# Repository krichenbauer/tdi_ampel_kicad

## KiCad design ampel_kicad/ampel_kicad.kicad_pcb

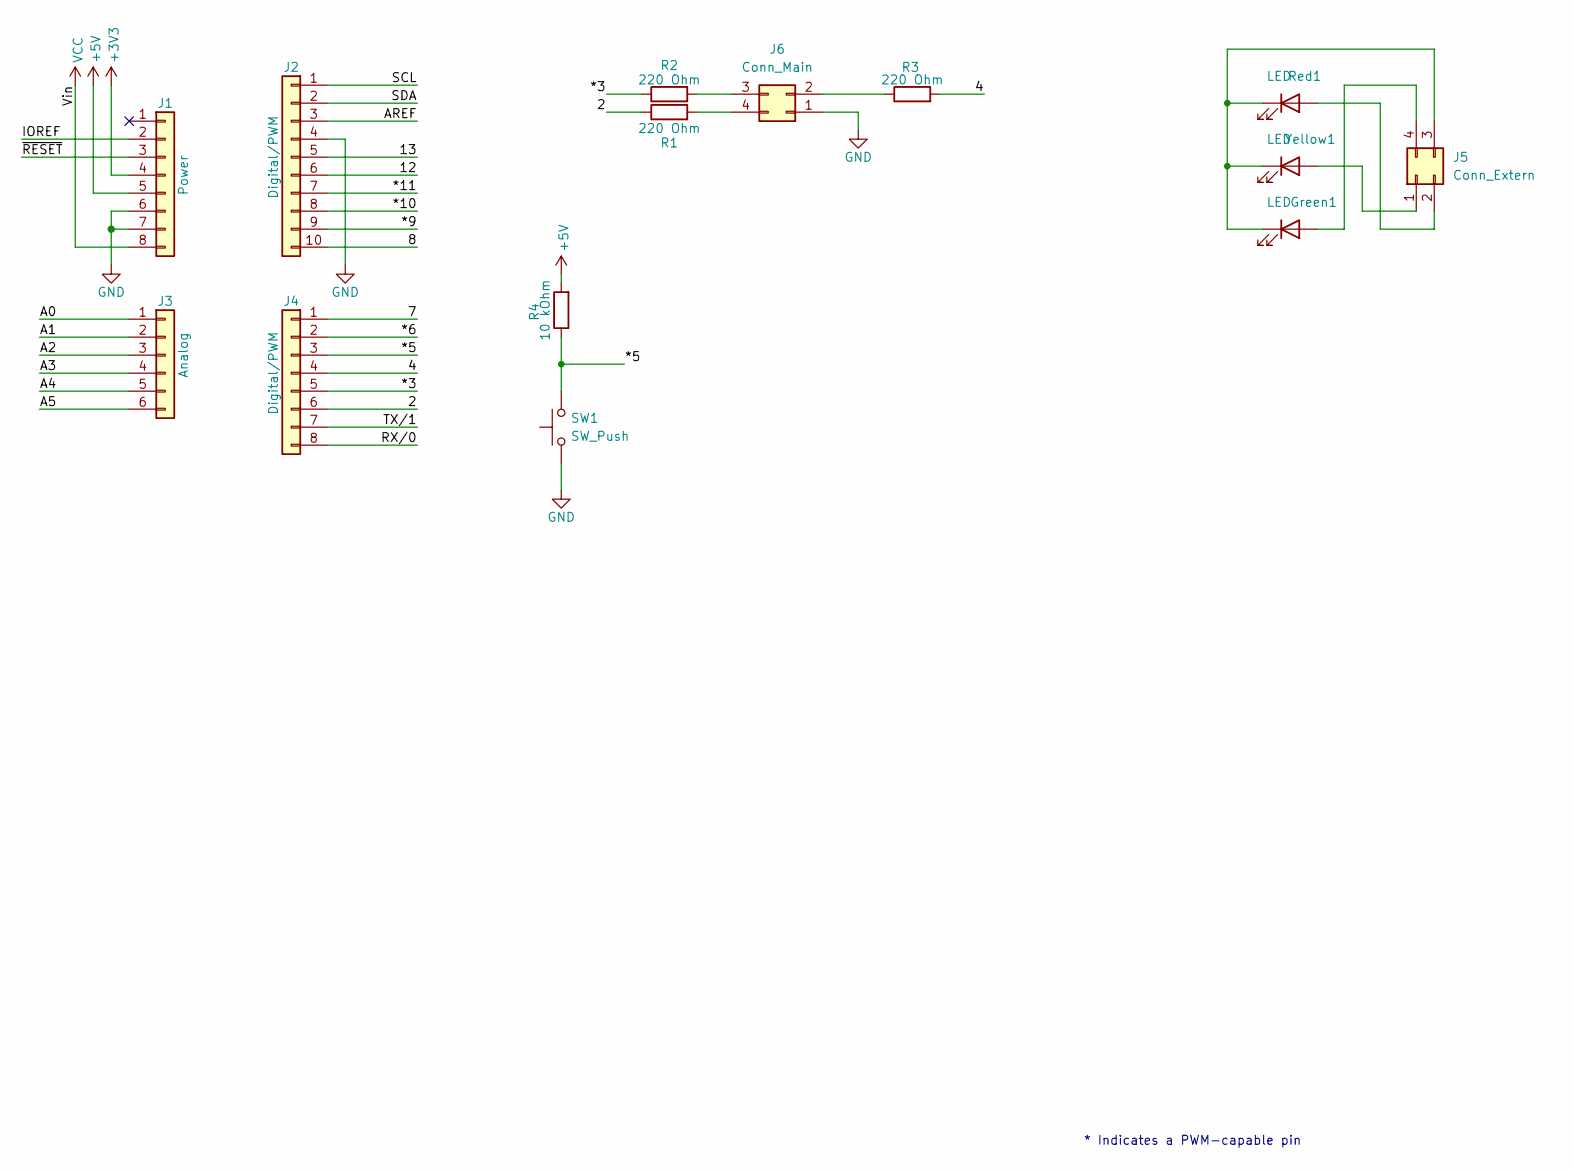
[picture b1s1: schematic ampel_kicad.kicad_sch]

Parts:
Green1: LED; LED_D3.0mm
J1: Power; PinSocket_1x08_P2.54mm_Vertical
J2: Digital/PWM; PinSocket_1x10_P2.54mm_Vertical
J3: Analog; PinSocket_1x06_P2.54mm_Vertical
J4: Digital/PWM; PinSocket_1x08_P2.54mm_Vertical
J5: Conn_Extern; PinSocket_2x02_P2.54mm_Vertical
J6: Conn_Main; PinSocket_2x02_P2.54mm_Vertical
R1, R2, R3: 220 Ohm; R_Axial_DIN0207_L6.3mm_D2.5mm_P7.62mm_Horizontal
R4: 10 kOhm; R_Axial_DIN0207_L6.3mm_D2.5mm_P7.62mm_Horizontal
Red1: LED; LED_D3.0mm
SW1: SW_Push; SW_PUSH_6mm
Yellow1: LED; LED_D3.0mm

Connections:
+3V3: J1.4
+5V: J1.5, R4.2; also elsewhere on the board
/2: J4.6, R1.1
/4: J4.4, R3.2
/7: J4.1
/8: J2.10
/12: J2.6
/13: J2.5
/*3: J4.5, R2.1
/*5: J4.3, R4.1, SW1.2; also elsewhere on the board
/*6: J4.2
/*9: J2.9
/*10: J2.8
/*11: J2.7
/A0: J3.1
/A1: J3.2
/A2: J3.3
/A3: J3.4
/A4: J3.5
/A5: J3.6
/AREF: J2.3
/IOREF: J1.2
/RX/0: J4.8
/SCL: J2.1
/SDA: J2.2
/TX/1: J4.7
/~RESET: J1.3
GND: J1.6, J1.7, J2.4, J6.1, SW1.1
unnamed: Green1.2 (A), J5.4
unnamed: Green1.1 (K), J5.3, Red1.1 (K), Yellow1.1 (K)
unnamed: J5.1, Yellow1.2 (A)
unnamed: J5.2, Red1.2 (A)
unnamed: J6.2, R3.1
unnamed: J6.3, R2.2
unnamed: J6.4, R1.2
VCC: J1.8

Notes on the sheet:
* Indicates a PWM-capable pin

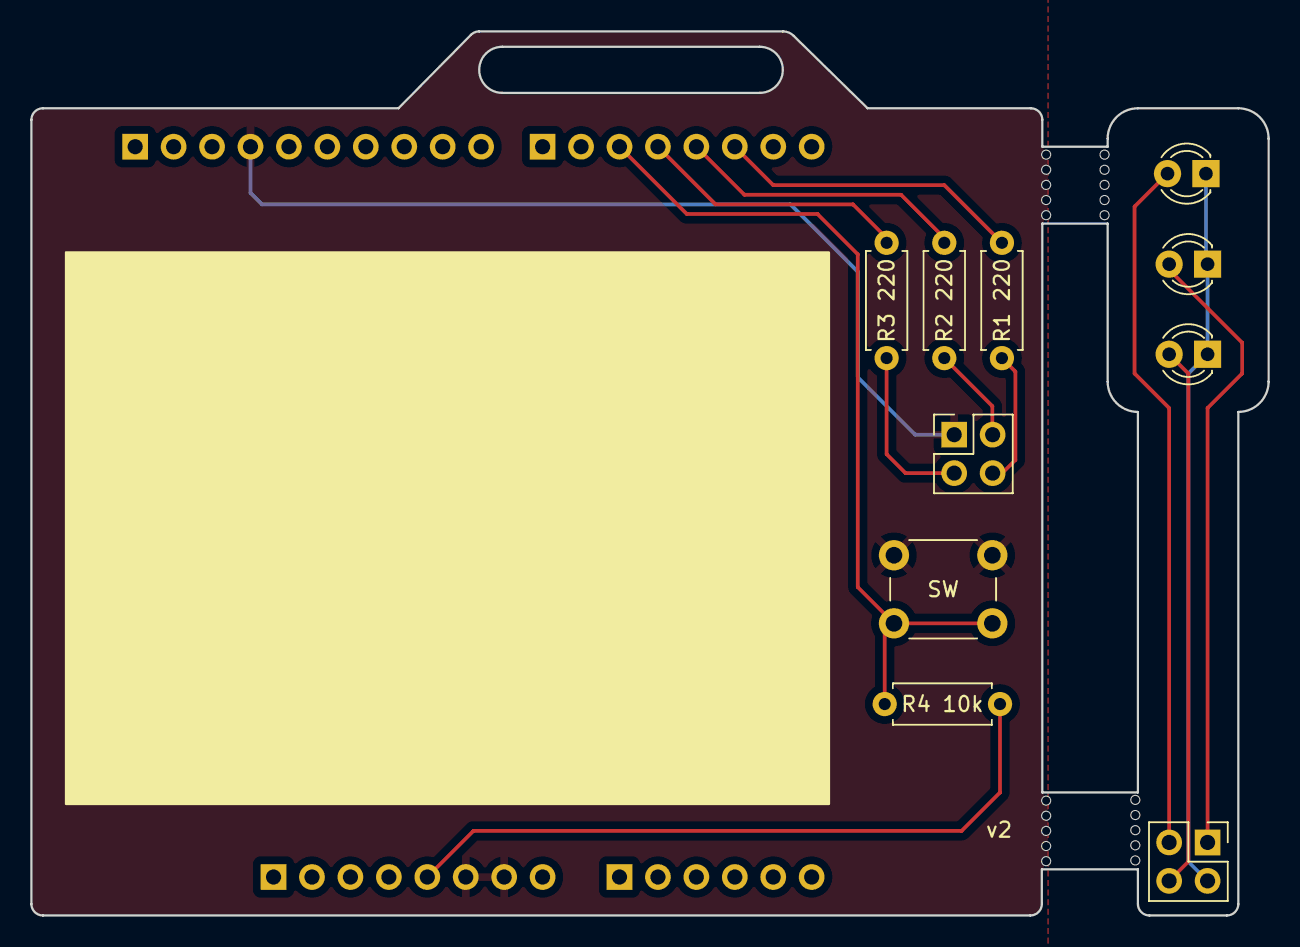
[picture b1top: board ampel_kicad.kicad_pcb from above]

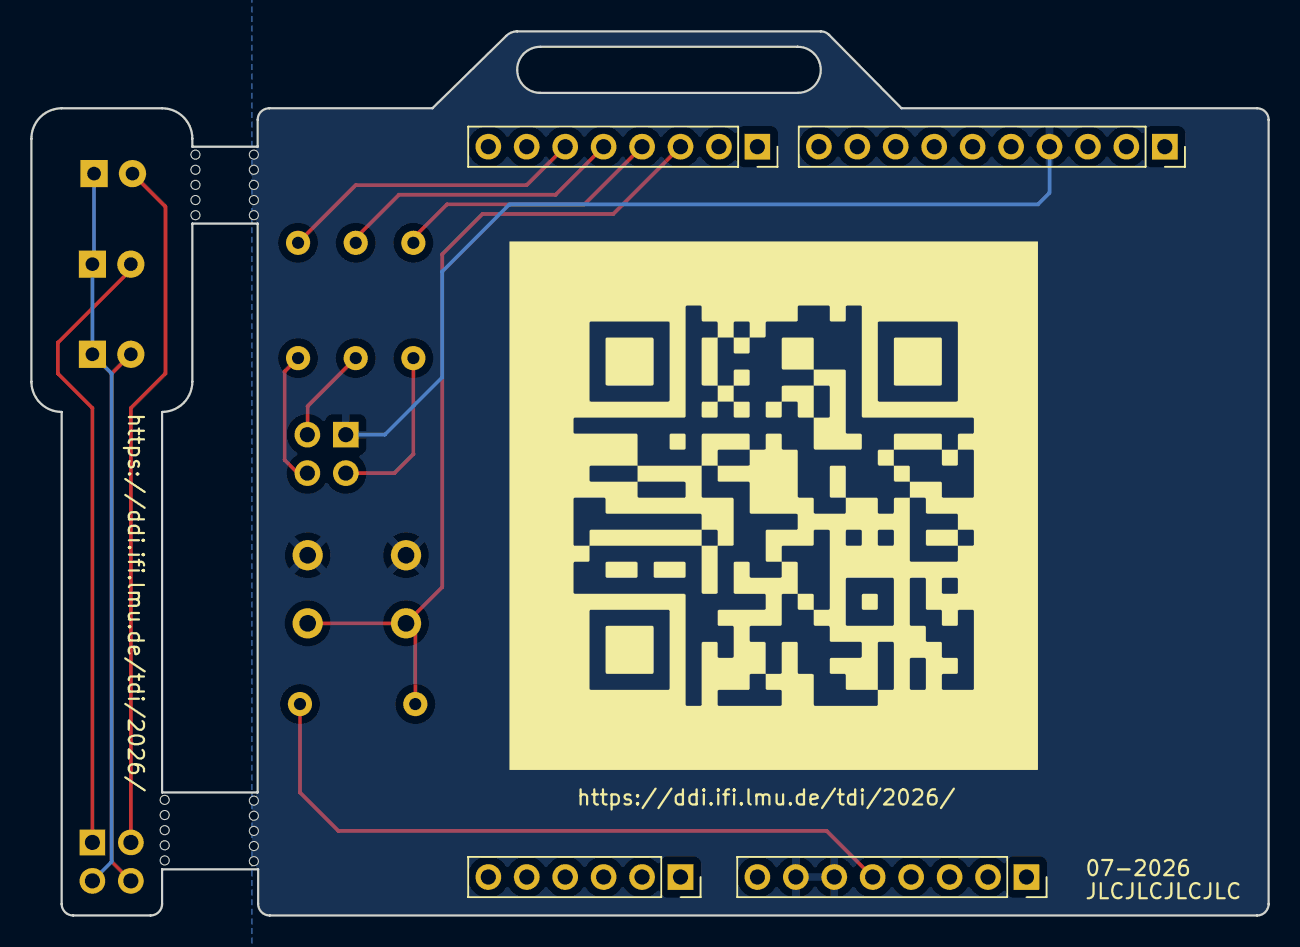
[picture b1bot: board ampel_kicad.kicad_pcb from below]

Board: 2 copper layers, 81.8 x 58.4 mm, 14 parts (4 on the bottom side), 13 nets.

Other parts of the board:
R4 10k: 10 kOhm; R_Axial_DIN0207_L6.3mm_D2.5mm_P7.62mm_Horizontal

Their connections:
+5V: R4 10k.2; also elsewhere on the board
/*5: R4 10k.1; also elsewhere on the board

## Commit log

2026-05-09 check
2026-05-12 update: no debounce
2026-05-12 JLC-Badge_Number + Date
2026-05-12 Exported files for order
